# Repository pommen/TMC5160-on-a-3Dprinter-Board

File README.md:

# TMC5160 on a 3Dprinter Board
 TMC5160 using the pinheaders on a typical 3d printer controllerboard as inputs via an adapter board to a bigger general purpose tmc5160 50V 3-5A (Goal)

V2

Features:
TMC5160a stepper driver with an external H-bridge.
Abillity to run at 48VDC with any 3d printer baord.
5&3.3v logic signals with power-on controlled buffer.
Internal voltage regualtor from 48VDC to 12, 5 and 3.3V
breakouts for all control pins, to be used depending of controlscheme.

All files made in KICAD
(Work in progress)

StepstickAdaptor board plugs in to the 3d printer stepper driver slots and feeds io signals and levels through a standard ethernet cable to the Driver board(TMC51604Axis).

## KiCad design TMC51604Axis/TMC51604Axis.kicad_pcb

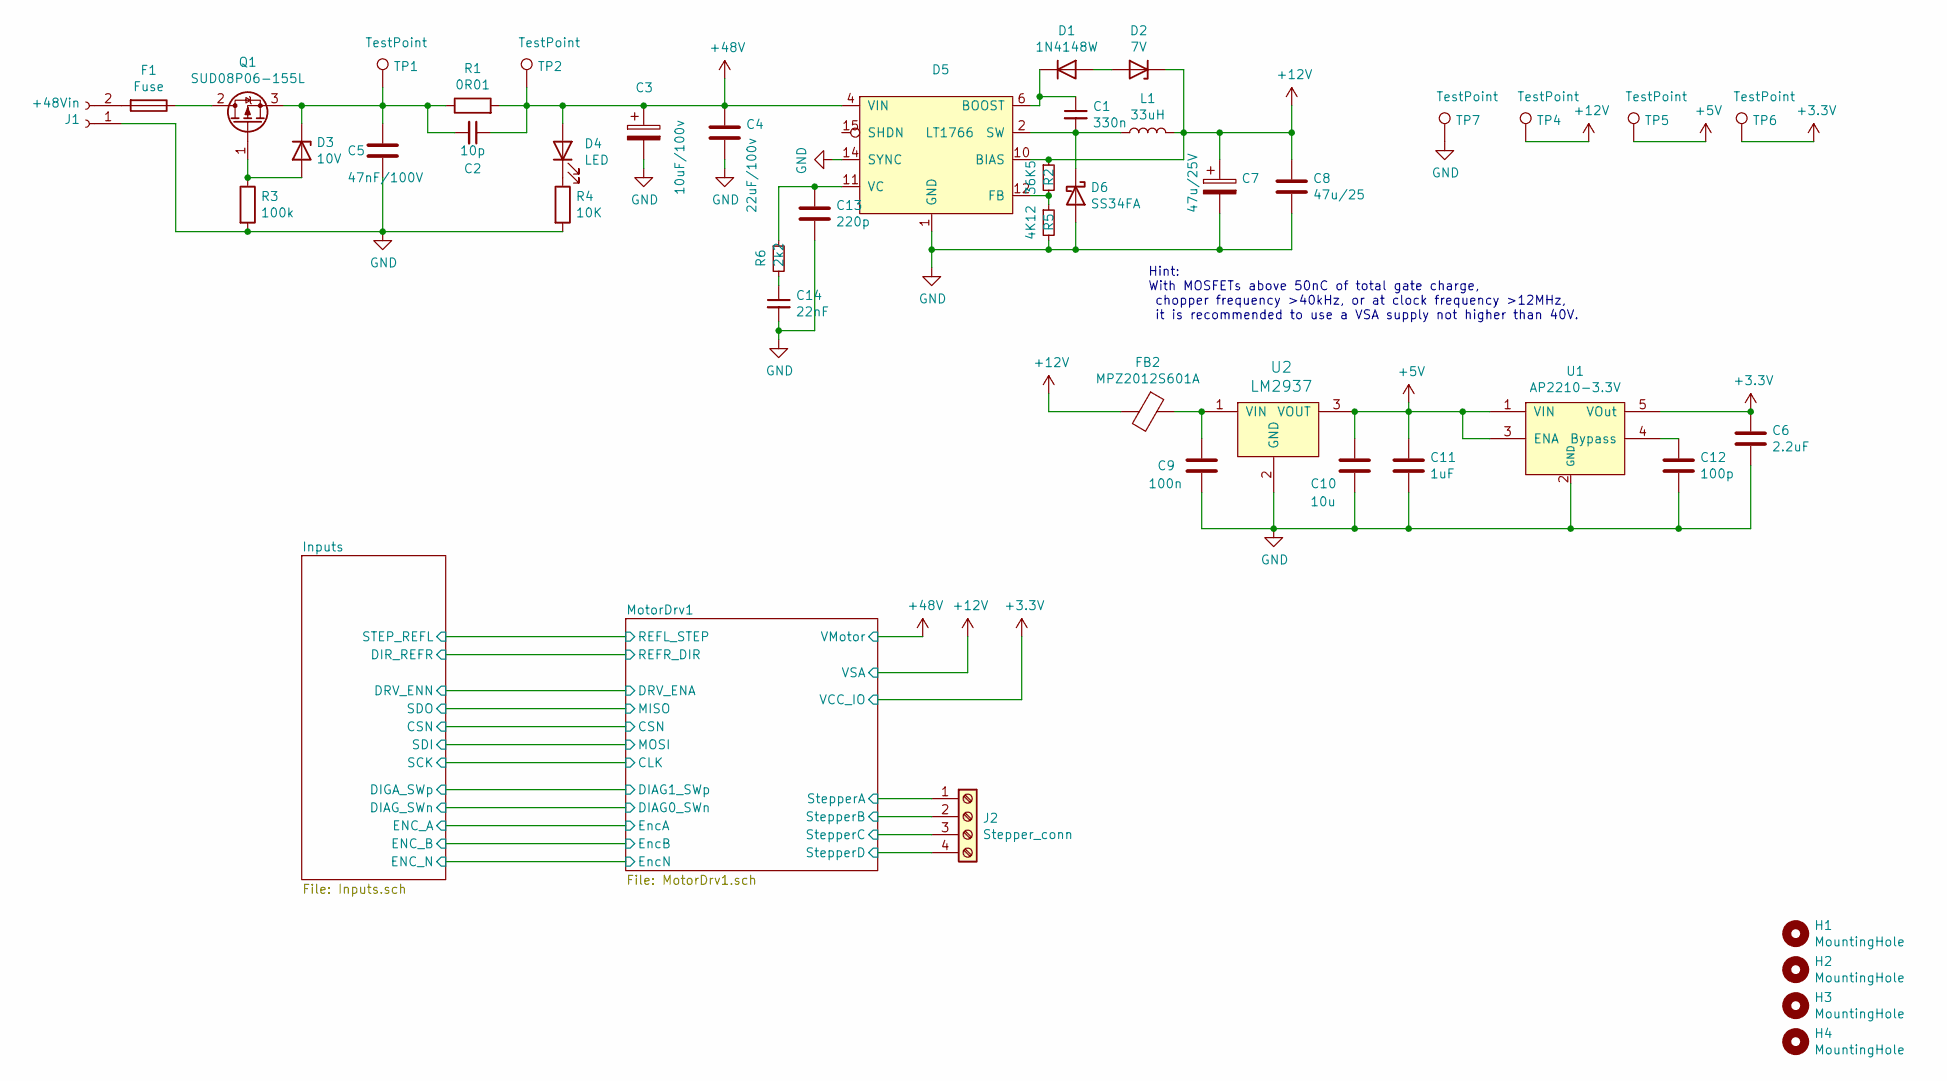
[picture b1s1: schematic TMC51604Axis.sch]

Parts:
C1: 330n; C_0805_peter
C2: 10p; C_0805_peter
C3: 10uF/100v; CP_Elec_8x6.2
C4: 22uF/100v; CP_Elec_8x6.2
C5: 47nF/100V; C_0805_peter
C6: 2.2uF; C_0805_peter
C7: 47u/25V; CP_Radial_D10.0mm_P5.00mm
C8: 47u/25; C_2010_5025Metric_Pad1.52x2.65mm_HandSolder
C9: 100n; C_0603_1608Metric
C10: 10u; C_0603_1608Metric
C11: 1uF; C_0805_peter
C12: 100p; C_0805_peter
C13: 220p; C_0805_peter
C14: 22nF; C_0805_peter
D1: 1N4148W; D_SOD-123
D2: 7V; D_1206_3216Metric
D3: 10V; D_1206_3216Metric
D4: LED; D_0805_2012Metric
D5: LT1766; TSSOP-16-1EP_4.4x5mm_P0.65mm
D6: SS34FA; D_SOD-123F
F1: Fuse; Fuse_2512_6332Metric
FB2: MPZ2012S601A; R_0805_2012Metric_Pad1.15x1.40mm_HandSolder
H1, H2, H3, H4: MountingHole; MountingHole_3.2mm_M3
J1: +48Vin; PhoenixContact_MSTB_2,5_2-GF_1x02_P5.00mm_Horizontal_Thread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
J2: Stepper_conn; TerminalBlock_Phoenix_PT-1,5-4-3.5-H_1x04_P3.50mm_Horizontal
L1: 33uH; L_7.3x7.3_H3.5
Q1: SUD08P06-155L; TO-252-2
R1: 0R01; R_2512_6332Metric
R2: 36K5; R_0805_peter
R3: 100k; R_0805_peter
R4: 10K; R_0805_peter
R5: 4K12; R_0805_peter
R6: 2k2; R_0805_peter
TP1, TP2: TestPoint; TestPoint_Pad_D1.5mm
TP4, TP5, TP6: TestPoint; TestPoint_Pad_1.5x1.5mm
TP7: TestPoint; TestPoint_THTPad_1.5x1.5mm_Drill0.7mm
U1: AP2210-3.3V; SOT-23-5_HandSoldering
U2: LM2937; SOT-223-3_TabPin2

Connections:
+5V: C10.1, C11.1, TP5.1, U1.1 (VIN), U1.3 (ENA), U2.3 (VOUT); also elsewhere on the board
+12V: C7.1, C8.1, D2.1 (K), D5.10 (BIAS), FB2.2, L1.2, R2.1, TP4.1; also elsewhere on the board
/MotorDrv1/StepperA: J2.4; also elsewhere on the board
/MotorDrv1/StepperB: J2.3; also elsewhere on the board
/MotorDrv1/StepperC: J2.2; also elsewhere on the board
/MotorDrv1/StepperD: J2.1; also elsewhere on the board
unnamed: C1.1, D1.1 (K), D5.6 (BOOST)
unnamed: C1.2, D5.2 (SW), D6.1 (K), L1.1
unnamed: C9.1, FB2.1, U2.1 (VIN)
unnamed: C12.1, U1.4 (Bypass)
unnamed: C13.1, D5.11 (VC), R6.1
unnamed: C14.1, R6.2
unnamed: D1.2 (A), D2.2 (A)
unnamed: D4.1 (K), R4.1
unnamed: D5.12 (FB), R2.2, R5.1
unnamed 76: F1.2, J1.2; also elsewhere on the board

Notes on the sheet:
Hint: With MOSFETs above 50nC of total gate charge, chopper frequency >40kHz, or at clock frequency >12MHz, it is recommended to use a VSA supply not higher than 40V.

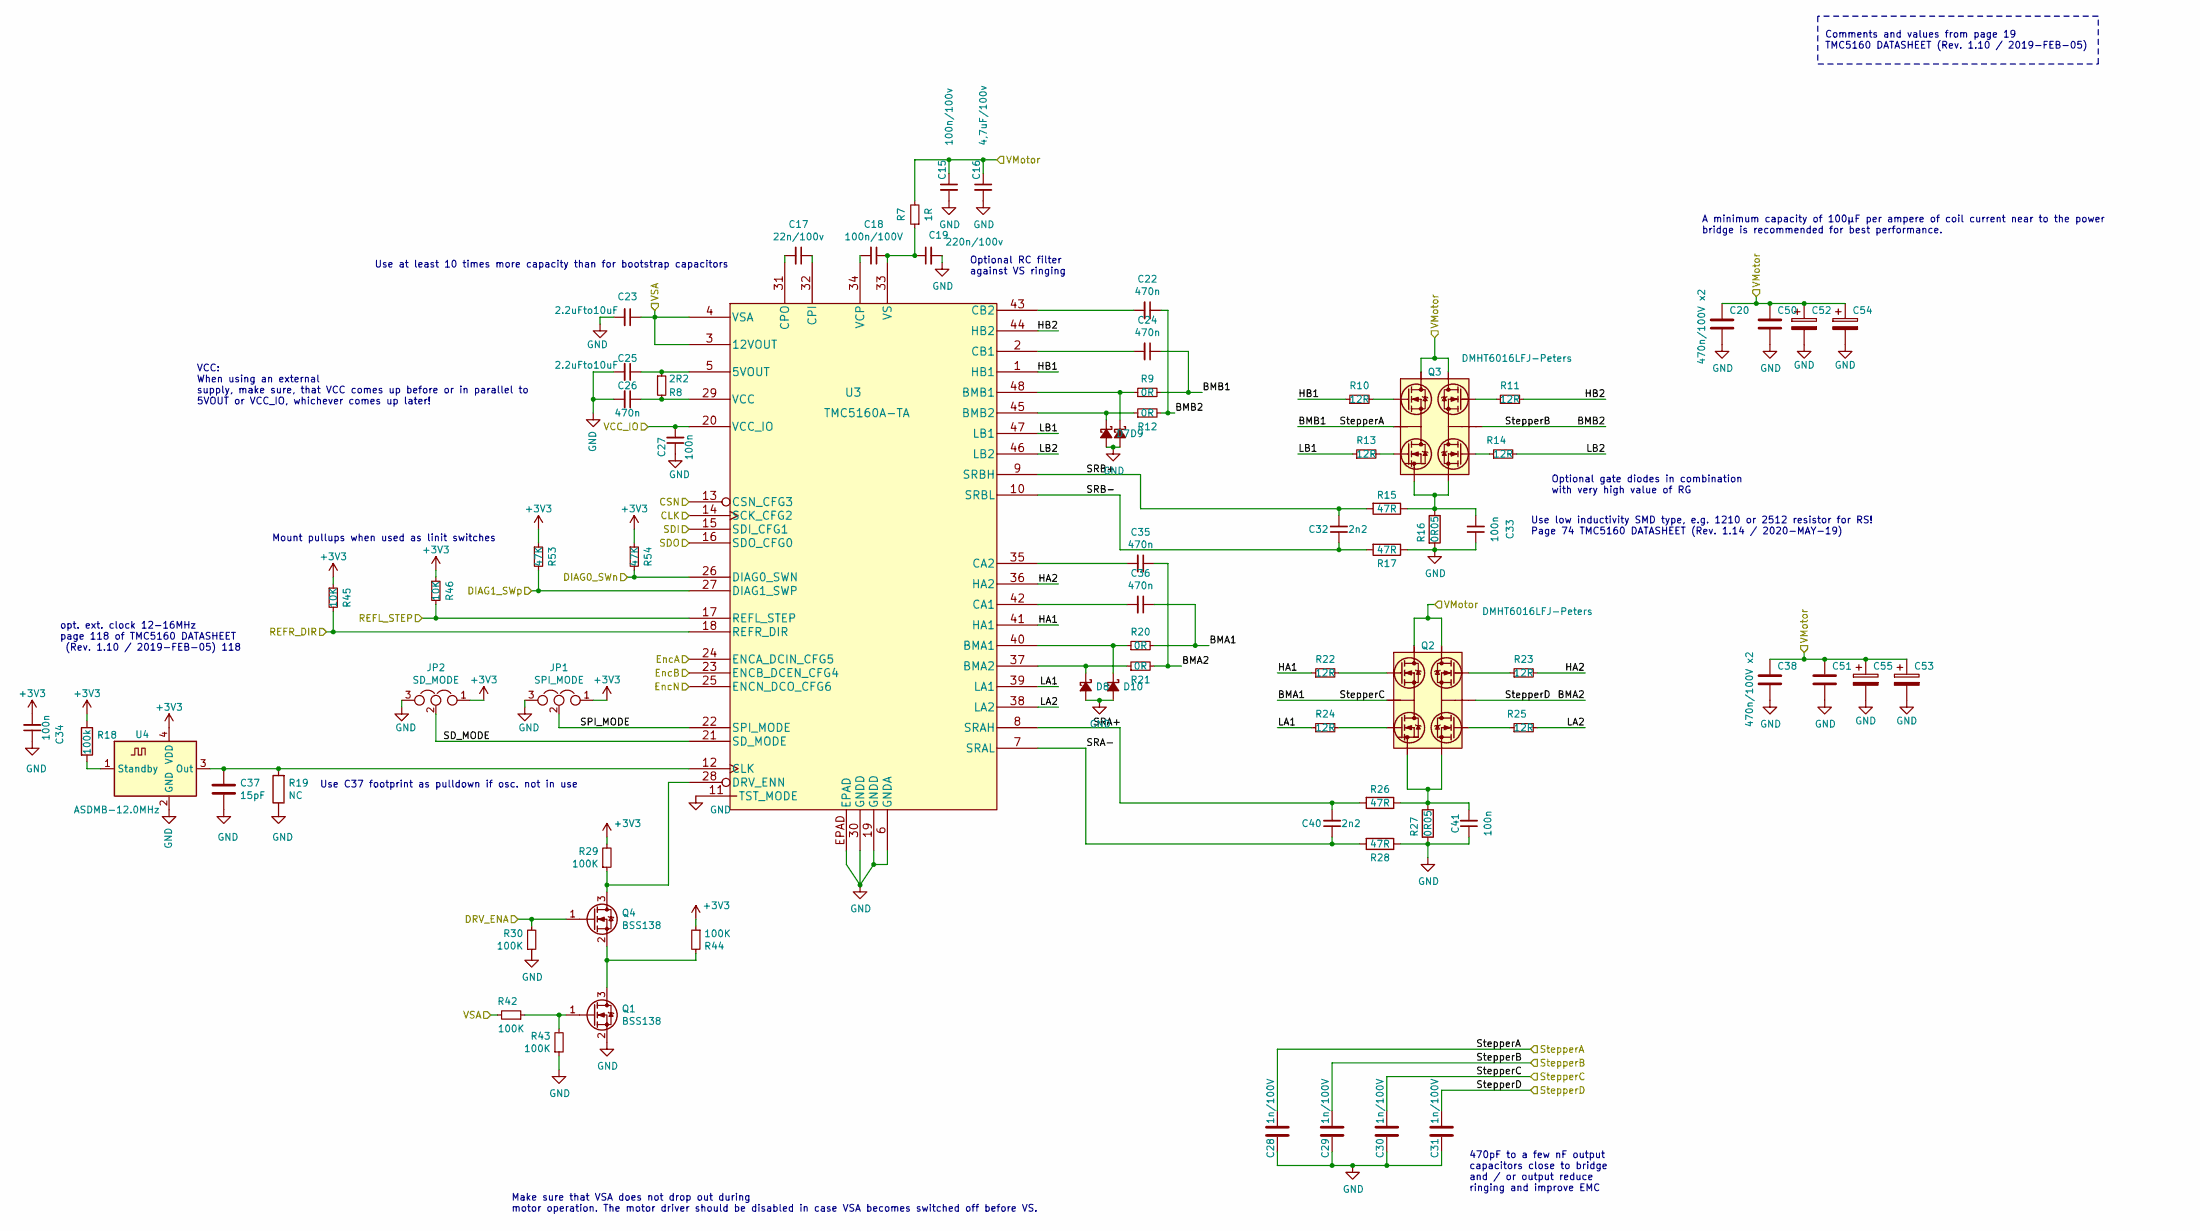
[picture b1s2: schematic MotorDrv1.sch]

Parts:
C15: 100n/100v; C_1206_3216Metric
C16: 4,7uF/100v; C_1206_3216Metric
C17: 22n/100v; C_0603_1608Metric; Digikery partno 445-2275-1-ND
C18: 100n/100V; C_0603_1608Metric
C19: 220n/100v; C_0805_2012Metric
C20, C38: 470n/100V x2; C_1206_3216Metric
C22, C24, C26, C35, C36: 470n; C_0603_1608Metric
C23, C25: 2.2uFto10uF; C_0603_1608Metric
C27, C33, C34, C41: 100n; C_0603_1608Metric
C28, C29, C30, C31: 1n/100V; C_0603_1608Metric
C32, C40: 2n2; C_0603_1608Metric
C37: 15pF; D_0805_peter
C50, C51: 470n/100V; C_1206_3216Metric
C52: 330uF/100V; CP_Radial_D12.5mm_P5.00mm; digikey# UVZ2A471MHD
C53, C54, C55: 330uF/100V; CP_Radial_D12.5mm_P5.00mm; digikey UVZ2A471MHD
D7, D8, D9, D10: PMEG6010CEGWX; D_SOD-123
JP1: SPI_MODE; SolderJumper-3_P1.3mm_Bridged12_RoundedPad1.0x1.5mm
JP2: SD_MODE; SolderJumper-3_P1.3mm_Bridged12_RoundedPad1.0x1.5mm
Q1, Q4: BSS138; SOT-23
Q2, Q3: DMHT6016LFJ-Peters; V-DFN5045-12 (Type B)
R7: 1R; R_0805_peter
R8: 2R2; R_0603_1608Metric
R9, R12, R20, R21: 0R; R_0603_1608Metric
R10, R11, R13, R14, R22, R23, R24, R25: 12R; R_0603_1608Metric
R15, R17, R26, R28: 47R; R_0603_1608Metric
R16, R27: 0R05; R_2512_6332Metric_Pad1.40x3.35mm_HandSolder
R18: 100k; R_0805_peter
R19: NC; R_0603_1608Metric
R29, R30, R42, R43, R44: 100K; R_0603_1608Metric
R45, R46: 10K; R_0603_1608Metric
R53, R54: 47K; R_0603_1608Metric
U3: TMC5160A-TA; LQFP-48-1EP_7x7mm_P0.5mm_EP3.6x3.6mm_peter
U4: ASDMB-12.0MHz; Oscillator_SMD_Abracon_ASDMB-4Pin_2.5x2.0mm

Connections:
+12V: C23.1, R42.2, U3.3 (12VOUT), U3.4 (VSA); also elsewhere on the board
/Inputs/CSN: U3.13 (CSN_CFG3); also elsewhere on the board
/Inputs/DIAG0_SWn: R54.2, U3.26 (DIAG0_SWN); also elsewhere on the board
/Inputs/DIAG1_SWp: R53.2, U3.27 (DIAG1_SWP); also elsewhere on the board
/Inputs/DIR_REFR: R45.2, U3.18 (REFR_DIR); also elsewhere on the board
/Inputs/ENC_A: U3.24 (ENCA_DCIN_CFG5); also elsewhere on the board
/Inputs/ENC_B: U3.23 (ENCB_DCEN_CFG4); also elsewhere on the board
/Inputs/ENC_N: U3.25 (ENCN_DCO_CFG6); also elsewhere on the board
/Inputs/SDI: U3.15 (SDI_CFG1); also elsewhere on the board
/Inputs/SDO: U3.16 (SDO_CFG0); also elsewhere on the board
/MotorDrv1/CLK: U3.14 (SCK_CFG2); also elsewhere on the board
/MotorDrv1/DRV_ENA: Q4.1 (G), R30.2; also elsewhere on the board
/MotorDrv1/HA1: R22.1, U3.41 (HA1)
/MotorDrv1/HA2: R23.2, U3.36 (HA2)
/MotorDrv1/HB1: R10.1, U3.1 (HB1)
/MotorDrv1/HB2: R11.2, U3.44 (HB2)
/MotorDrv1/LA1: R24.1, U3.39 (LA1)
/MotorDrv1/LA2: R25.2, U3.38 (LA2)
/MotorDrv1/LB1: R13.1, U3.47 (LB1)
/MotorDrv1/LB2: R14.2, U3.46 (LB2)
/MotorDrv1/REFL_STEP: R46.2, U3.17 (REFL_STEP); also elsewhere on the board
/MotorDrv1/SD_MODE: JP2.2, U3.21 (SD_MODE)
/MotorDrv1/SPI_MODE: JP1.2, U3.22 (SPI_MODE)
/MotorDrv1/SRA+: C40.2, R26.2, U3.8 (SRAH)
/MotorDrv1/SRA-: C40.1, R28.2, U3.7 (SRAL)
/MotorDrv1/SRB+: C32.2, R15.2, U3.9 (SRBH)
/MotorDrv1/SRB-: C32.1, R17.2, U3.10 (SRBL)
/MotorDrv1/StepperA: C24.1, C28.1, Q3.3 (S1/D2), Q3.14 (S1/D2), R9.2; also elsewhere on the board
/MotorDrv1/StepperB: C22.1, C29.1, Q3.10 (S4/D3), Q3.15 (S4/D3), R12.2; also elsewhere on the board
/MotorDrv1/StepperC: C30.1, C36.1, Q2.3 (S1/D2), Q2.14 (S1/D2), R20.2; also elsewhere on the board
/MotorDrv1/StepperD: C31.1, C35.1, Q2.10 (S4/D3), Q2.15 (S4/D3), R21.2; also elsewhere on the board
unnamed: C17.1, U3.32 (CPI)
unnamed: C17.2, U3.31 (CPO)
unnamed: C18.1, C19.1, R7.1, U3.33 (VS)
unnamed: C18.2, U3.34 (VCP)
unnamed: C22.2, U3.43 (CB2)
unnamed: C24.2, U3.2 (CB1)
unnamed: C25.1, R8.1, U3.5 (5VOUT)
unnamed: C26.1, R8.2, U3.29 (VCC)
unnamed: C33.2, Q3.5 (S2), Q3.6 (S2), Q3.7 (S3), Q3.8 (S3), R15.1, R16.1
unnamed: C35.2, U3.35 (CA2)
unnamed: C36.2, U3.42 (CA1)
unnamed: C37.1, R19.2, U3.12 (CLK), U4.3 (Out)
unnamed: C41.2, Q2.5 (S2), Q2.6 (S2), Q2.7 (S3), Q2.8 (S3), R26.1, R27.1
unnamed: D7.1 (K), R12.1, U3.45 (BMB2)
unnamed: D8.1 (K), R21.1, U3.37 (BMA2)
unnamed: D9.1 (K), R9.1, U3.48 (BMB1)
unnamed: D10.1 (K), R20.1, U3.40 (BMA1)
unnamed: Q2.1 (G1), R22.2
unnamed: Q2.4 (G2), R24.2
unnamed: Q2.9 (G3), R25.1
unnamed: Q2.12 (G4), R23.1
unnamed: Q3.1 (G1), R10.2
unnamed: Q3.4 (G2), R13.2
unnamed: Q3.9 (G3), R14.1
unnamed: Q3.12 (G4), R11.1
unnamed: Q4.3 (D), R29.1, U3.28 (DRV_ENN)
unnamed: R18.2, U4.1 (Standby)

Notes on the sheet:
Use at least 10 times more capacity than for bootstrap capacitors
opt. ext. clock 12-16MHz page 118 of TMC5160 DATASHEET (Rev. 1.10 / 2019-FEB-05) 118
Use low inductivity SMD type, e.g. 1210 or 2512 resistor for RS! Page 74 TMC5160 DATASHEET (Rev. 1.14 / 2020-MAY-19)
Comments and values from page 19 TMC5160 DATASHEET (Rev. 1.10 / 2019-FEB-05)
Optional gate diodes in combination with very high value of RG
Optional RC filter against VS ringing
A minimum capacity of 100µF per ampere of coil current near to the power bridge is recommended for best performance.
470pF to a few nF output capacitors close to bridge and / or output reduce ringing and improve EMC
VCC: When using an external supply, make sure, that VCC comes up before or in parallel to 5VOUT or VCC_IO, whichever comes up later!
Use C37 footprint as pulldown if osc. not in use
Make sure that VSA does not drop out during motor operation. The motor driver should be disabled in case VSA becomes switched off before VS.
Mount pullups when used as linit switches

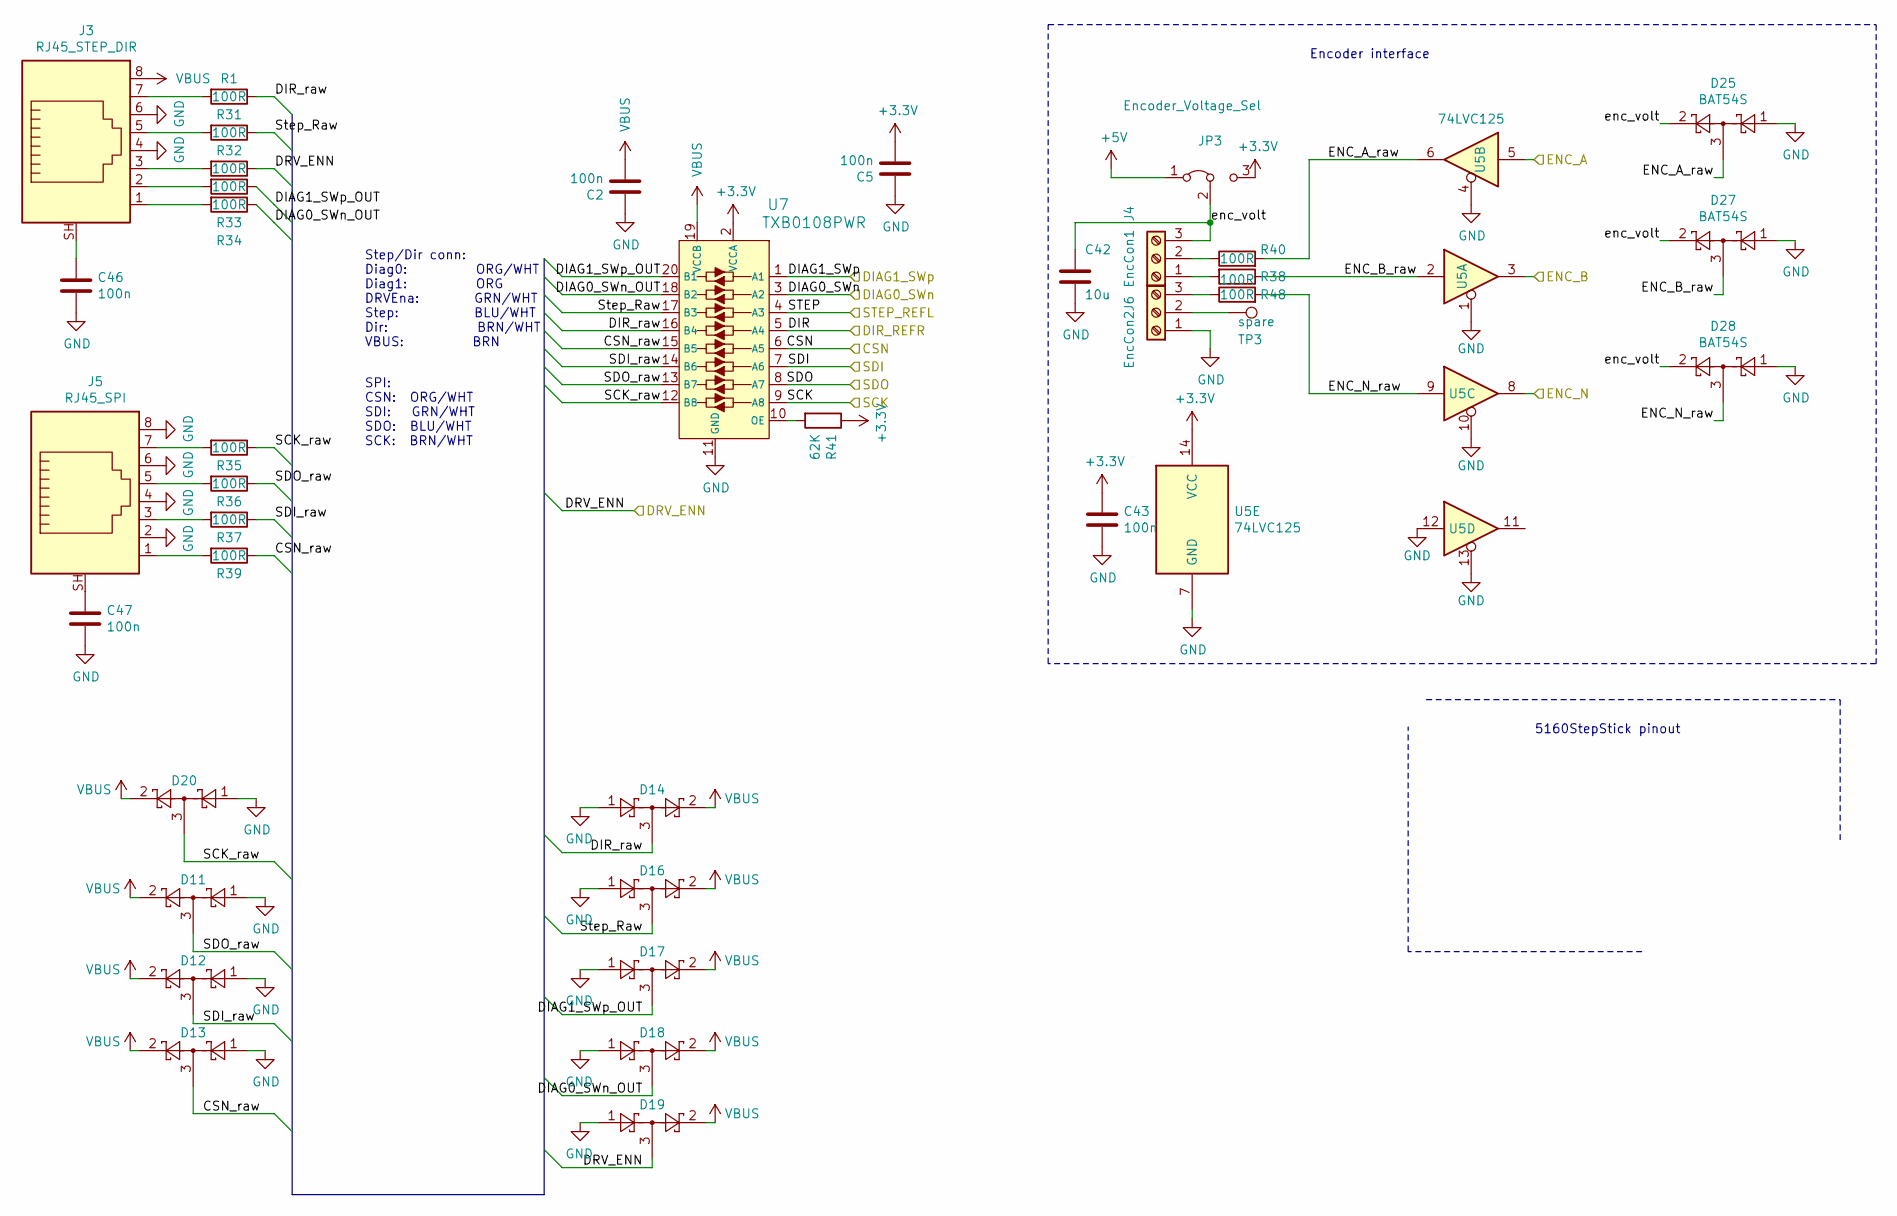
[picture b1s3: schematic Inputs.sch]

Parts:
C2, C5: 100n; C_0603_1608Metric
C42: 10u; C_0805_peter
C43, C46, C47: 100n; C_0805_peter
D11, D12, D13, D14, D16, D17, D18, D19, D20, D25, D27, D28: BAT54S; SOT-23
J3: RJ45_STEP_DIR; 360s-1812-11001(RJ45)
J4: EncCon1; TerminalBlock_Phoenix_PT-1,5-3-3.5-H_1x03_P3.50mm_Horizontal
J5: RJ45_SPI; 360s-1812-11001(RJ45)
J6: EncCon2; TerminalBlock_Phoenix_PT-1,5-3-3.5-H_1x03_P3.50mm_Horizontal
JP3: Encoder_Voltage_Sel; SolderJumper-3_P2.0mm_Open_TrianglePad1.0x1.5mm
R1, R31, R32, R33, R34, R35, R36, R37, R38, R39, R40, R48: 100R; R_0603_1608Metric
R41: 62K; C_0805_peter
TP3: spare; TestPoint_THTPad_1.0x1.0mm_Drill0.5mm
U5: 74LVC125; SO-14_3.9x8.65mm_P1.27mm
U7: TXB0108PWR; TSSOP-20_W4.4mm; MPN TXB0108PWR; Digi-Key_PN 296-21527-1-ND

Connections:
+5V: JP3.1 (A); also elsewhere on the board
/Inputs/CSN: U7.6 (A5); also elsewhere on the board
/Inputs/CSN_raw: D13.3, R39.1, U7.15 (B5)
/Inputs/DIAG0_SWn: U7.3 (A2); also elsewhere on the board
/Inputs/DIAG0_SWn_OUT: D18.3, R34.1, U7.18 (B2)
/Inputs/DIAG1_SWp: U7.1 (A1); also elsewhere on the board
/Inputs/DIAG1_SWp_OUT: D17.3, R33.1, U7.20 (B1)
/Inputs/DIR_REFR: U7.5 (A4); also elsewhere on the board
/Inputs/ENC_A: U5.5; also elsewhere on the board
/Inputs/ENC_A_raw: D25.3, R40.2, U5.6
/Inputs/ENC_B: U5.3; also elsewhere on the board
/Inputs/ENC_B_raw: D27.3, R38.1, U5.2
/Inputs/ENC_N: U5.8; also elsewhere on the board
/Inputs/ENC_N_raw: D28.3, R48.2, U5.9
/Inputs/SCK_raw: D20.3, R35.1, U7.12 (B8)
/Inputs/SDI: U7.7 (A6); also elsewhere on the board
/Inputs/SDI_raw: D12.3, R37.1, U7.14 (B6)
/Inputs/SDO: U7.8 (A7); also elsewhere on the board
/Inputs/SDO_raw: D11.3, R36.1, U7.13 (B7)
/Inputs/Step_Raw: D16.3, R31.1, U7.17 (B3)
/Inputs/enc_volt: C42.1, D25.2, D27.2, D28.2, J4.3, JP3.2 (C)
/MotorDrv1/CLK: U7.9 (A8); also elsewhere on the board
/MotorDrv1/DRV_ENA: D19.3, R32.1; also elsewhere on the board
/MotorDrv1/REFL_STEP: U7.4 (A3); also elsewhere on the board
unnamed: C46.1, J3.SH
unnamed: C47.1, J5.SH
unnamed: J3.1, R34.2
unnamed: J3.2, R33.2
unnamed: J3.3, R32.2
unnamed: J3.5, R31.2
unnamed: J4.1, R38.2
unnamed: J4.2, R40.1
unnamed: J5.1, R39.2
unnamed: J5.3, R37.2
unnamed: J5.5, R36.2
unnamed: J5.7, R35.2
unnamed: J6.2, TP3.1
unnamed: J6.3, R48.1
unnamed: R41.2, U7.10 (OE)

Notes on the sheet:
5160StepStick pinout
Encoder interface
SPI: CSN: ORG/WHT SDI: GRN/WHT SDO: BLU/WHT SCK: BRN/WHT
Step/Dir conn: Diag0: ORG/WHT Diag1: ORG DRVEna: GRN/WHT Step: BLU/WHT Dir: BRN/WHT VBUS: BRN

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
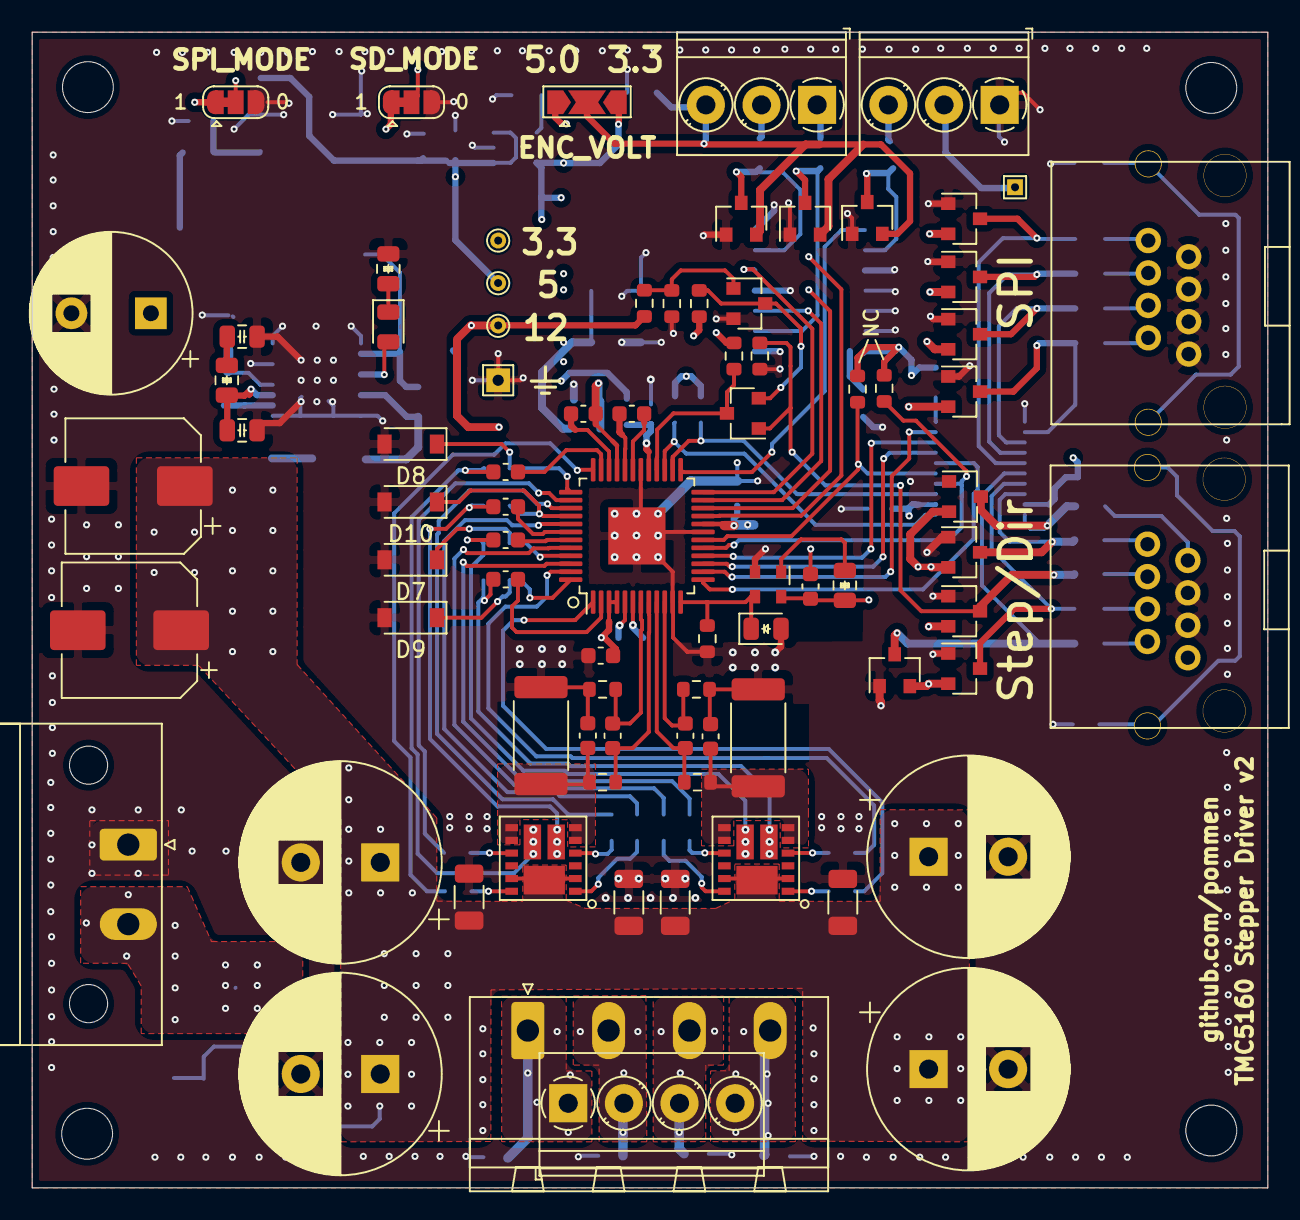
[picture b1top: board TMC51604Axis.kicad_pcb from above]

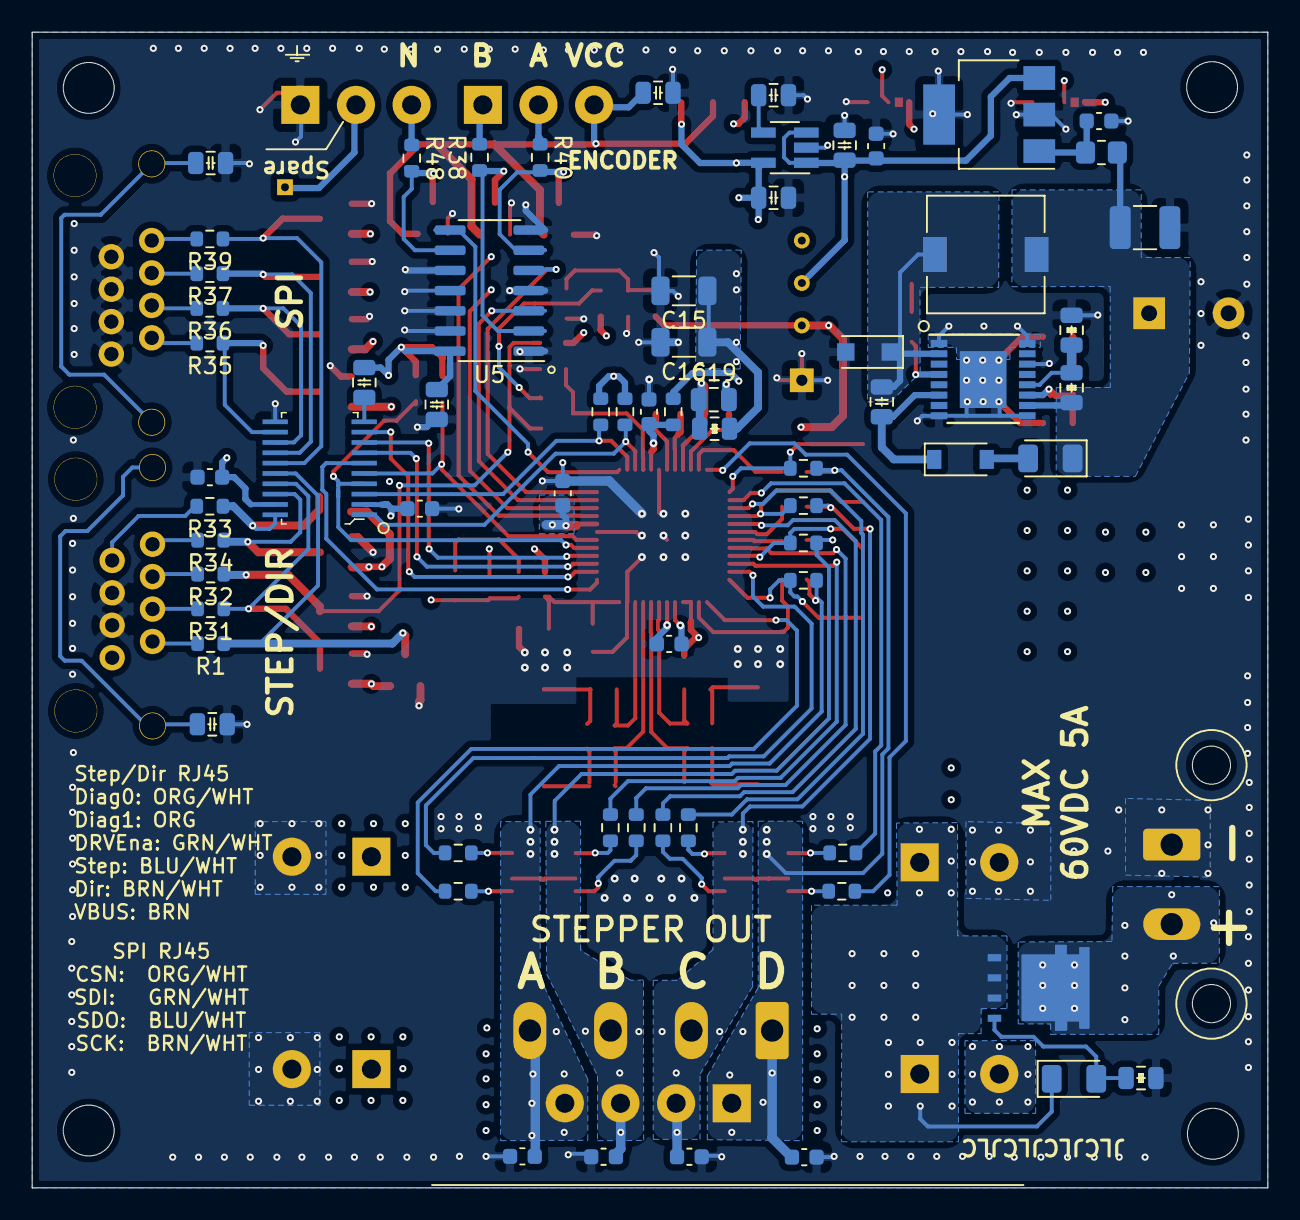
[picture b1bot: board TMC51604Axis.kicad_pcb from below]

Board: 4 copper layers, 77.7 x 72.7 mm, 152 parts (67 on the bottom side), 104 nets.

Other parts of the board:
J7: Stepper_conn; PhoenixContact_MSTBA_2,5_4-G-5,08_1x04_P5.08mm_Horizontal
Q5: SQJ481EP; PowerPAK SO-8L SINGLE

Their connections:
/MotorDrv1/StepperA: J7.4; also elsewhere on the board
/MotorDrv1/StepperB: J7.3; also elsewhere on the board
/MotorDrv1/StepperC: J7.2; also elsewhere on the board
/MotorDrv1/StepperD: J7.1; also elsewhere on the board
unnamed 76: Q5.5; also elsewhere on the board

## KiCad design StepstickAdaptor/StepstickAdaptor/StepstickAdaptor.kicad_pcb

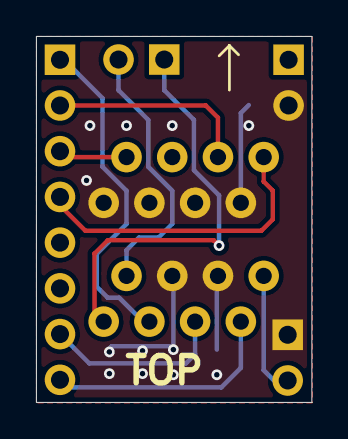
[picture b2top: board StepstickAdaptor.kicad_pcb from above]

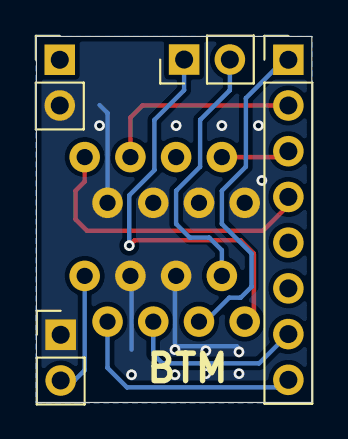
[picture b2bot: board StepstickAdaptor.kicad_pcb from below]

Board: 4 copper layers, 15.3 x 20.3 mm, 5 parts (4 on the bottom side), 11 nets.

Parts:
J1: E5908-0T0343-L
J2: Conn_01x08_Male; PinHeader_1x08_P2.54mm_Vertical
J4, J5, J6: Conn_01x02_Male; PinHeader_1x02_P2.54mm_Vertical

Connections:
/Diag1: J1.1, J4.1
/ENCN: J1.2, J4.2
/csn: J1.9, J2.4
/dir: J1.7, J2.8
/en: J1.3, J2.1
/sck: J1.15, J2.3
/sdi: J1.11, J2.2
/sdo: J1.13, J2.6
/step: J1.5, J2.7
GND: J1.4, J1.6, J1.10, J1.12, J1.14, J1.16, J5.2, J6.1
VCC: J1.8, J6.2

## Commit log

2019-10-03 sync
2020-05-30 Layout done! Still untested
2020-05-30 Redone input section
2020-05-30 Ver0.1 done
2020-05-30 Ver 0.1 sync
2020-06-13 Bug fixes during first assembly
2020-06-14 updated todo's
2020-06-14 updated todo
2021-01-05 First layout V2
2021-01-05 cleanup
2021-01-14 correced silk top
